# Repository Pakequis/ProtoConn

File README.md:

[![CC BY-SA 4.0][cc-by-sa-shield]][cc-by-sa]
# ProtoConn
A prototype board with connectors for electronic testing and development

This work is licensed under a
[Creative Commons Attribution-ShareAlike 4.0 International License][cc-by-sa].

[![CC BY-SA 4.0][cc-by-sa-image]][cc-by-sa]

[cc-by-sa]: http://creativecommons.org/licenses/by-sa/4.0/
[cc-by-sa-image]: https://licensebuttons.net/l/by-sa/4.0/88x31.png
[cc-by-sa-shield]: https://img.shields.io/badge/License-CC%20BY--SA%204.0-lightgrey.svg

### Overview

This open-hardware prototype board was created as a practical tool to simplify and speed up prototyping. With connectors for various functions, it’s designed to make development more flexible and efficient.

## Demo video:

### Features

Size: 200 x 195 mm dual layer PCB.
- **DE-9 Connector**: Supports serial, joystick, or CAN communication.
- **RCA Connectors**: Includes 3 RCA connectors.
- **Audio Connectors**:
  - 1 P2 audio jack (up to 4 pins).
  - 1 6.3 mm audio jack.
- **Screw Terminals**: Includes 2 screw terminals, one dedicated to power supply.
- **Barrel Connector**: For power input, with integrated 78XX voltage regulator and on/off switch.
- **Potentiometer or Rotary Encoder**: For adjustable input functionality.
- **40-Pin I/O Connector**: Compatible with Raspberry Pi and other Single Board Computers (SBCs).
- **JTAG Connector**: Standard 20-pin JTAG interface.
- **SWD Connectors**:
  - 10-pin SWD with 2.54 mm pitch.
  - 10-pin SWD with 1.27 mm pitch.
- **Programming Connector**: 4-pin interface for STM32 programming.
- **USB/Serial Converter Connector**: Simplifies communication setup.
- **Microcontroller Spaces**: Dedicated spaces for microcontroller boards with widths of 600, 700, 800, and 1000 mils.
- **Arduino Shield Compatibility**: Area for connecting Arduino-compatible shields.
- **Matrix Keypad**: Includes a 12-key matrix keypad.
- **LED Indicators**: 8 LEDs with current-limiting resistors.
- **USB Connectors**:
  - 1 USB Type-A connector.
  - 1 USB Type-B connector.
  - 1 USB Type-C connector.
- **Ground Pad**: Convenient GND pad for prototyping needs.

### Project Files
All project files are organized in the `hardware` folder. If you'd like to manufacture an identical board, the Gerber files necessary for production are available in the `hardware/fab` folder.

Please note that the board does not need to be assembled exactly as shown in the photo. You are free to assemble only the components you want or need, tailoring it to your specific requirements.

Because of this flexibility, the project does not include a complete bill of materials (BOM). Please refer to the notes in the schematic diagram for more detailed information.

Below is an example of an assembled board featuring common black connectors:

## Recommended Components

Here are some specific components that can be used with this board, along with links to purchase them:

- **Colorful Breakable Pin Header 2.54mm Single Row Male**: [Aliexpress](https://s.click.aliexpress.com/e/_op1UJvb)
- **Colorful Breakable Pin Header 2.54mm Single Row Female**: [Aliexpress](https://s.click.aliexpress.com/e/_oB8GhPJ)
- **40-Pin Header for Raspberry Pi**: [Aliexpress](https://s.click.aliexpress.com/e/_oCoQNaN)
- **USB Type-C 02 Connector**: [Aliexpress](https://s.click.aliexpress.com/e/_oo63JmH)
- **Power switch**: [Aliexpress](https://s.click.aliexpress.com/e/_oD5kKvX)

The other components are common and easy to find.

**Affiliate Disclosure**: Some of the links provided in this section are affiliate links. This means that I may earn a commission if you make a purchase through these links, at no additional cost to you. Your support helps to maintain and improve this project.

### Connector Areas

Below are images showcasing the connector areas of the board:

### Top Connector Area

### Bottom Connector Area

### Project Background:
Almost 20 years ago, I purchased a commercial prototype board with multiple connectors that greatly facilitated my work. Unfortunately, I no longer remember where I bought it, and I am unsure if it is still being manufactured. This inspired me to create my own version, customized to meet my specific needs.

The board (circa 2008):

## Contact:

Feel free to reach out to me on social media: @pakequis in any of them...

You can also send me an email at pakequis (Gmail).

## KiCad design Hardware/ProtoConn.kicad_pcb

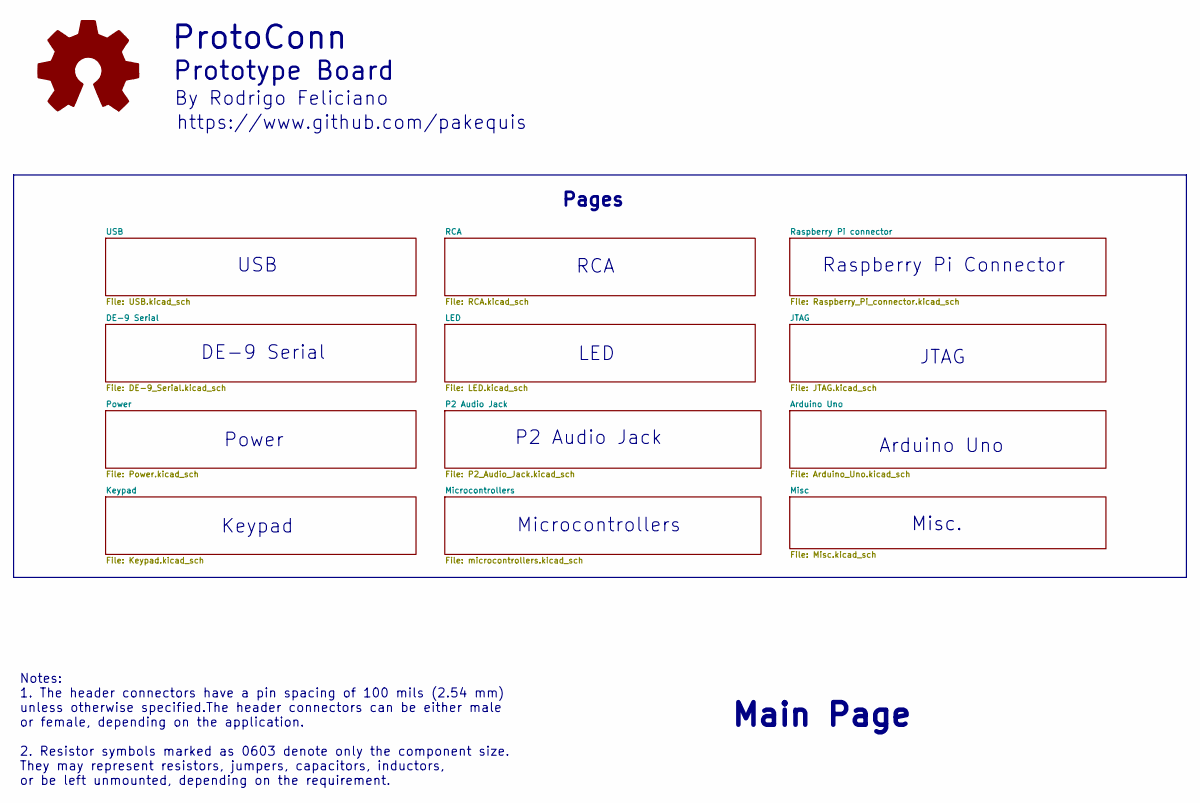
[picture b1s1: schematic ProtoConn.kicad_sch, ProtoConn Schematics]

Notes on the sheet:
USB
Main Page
P2 Audio Jack
Arduino Uno
Microcontrollers
Notes: 1. The header connectors have a pin spacing of 100 mils (2.54 mm) unless otherwise specified.The header connectors can be either male or female, depending on the application. 2. Resistor symbols marked as 0603 denote only the component size. They may represent resistors, jumpers, capacitors,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
Pages
Raspberry Pi Connector
https://www.github.com/pakequis
RCA
Power
JTAG
Keypad
DE-9 Serial
Misc.
LED
Prototype Board
ProtoConn
By Rodrigo Feliciano

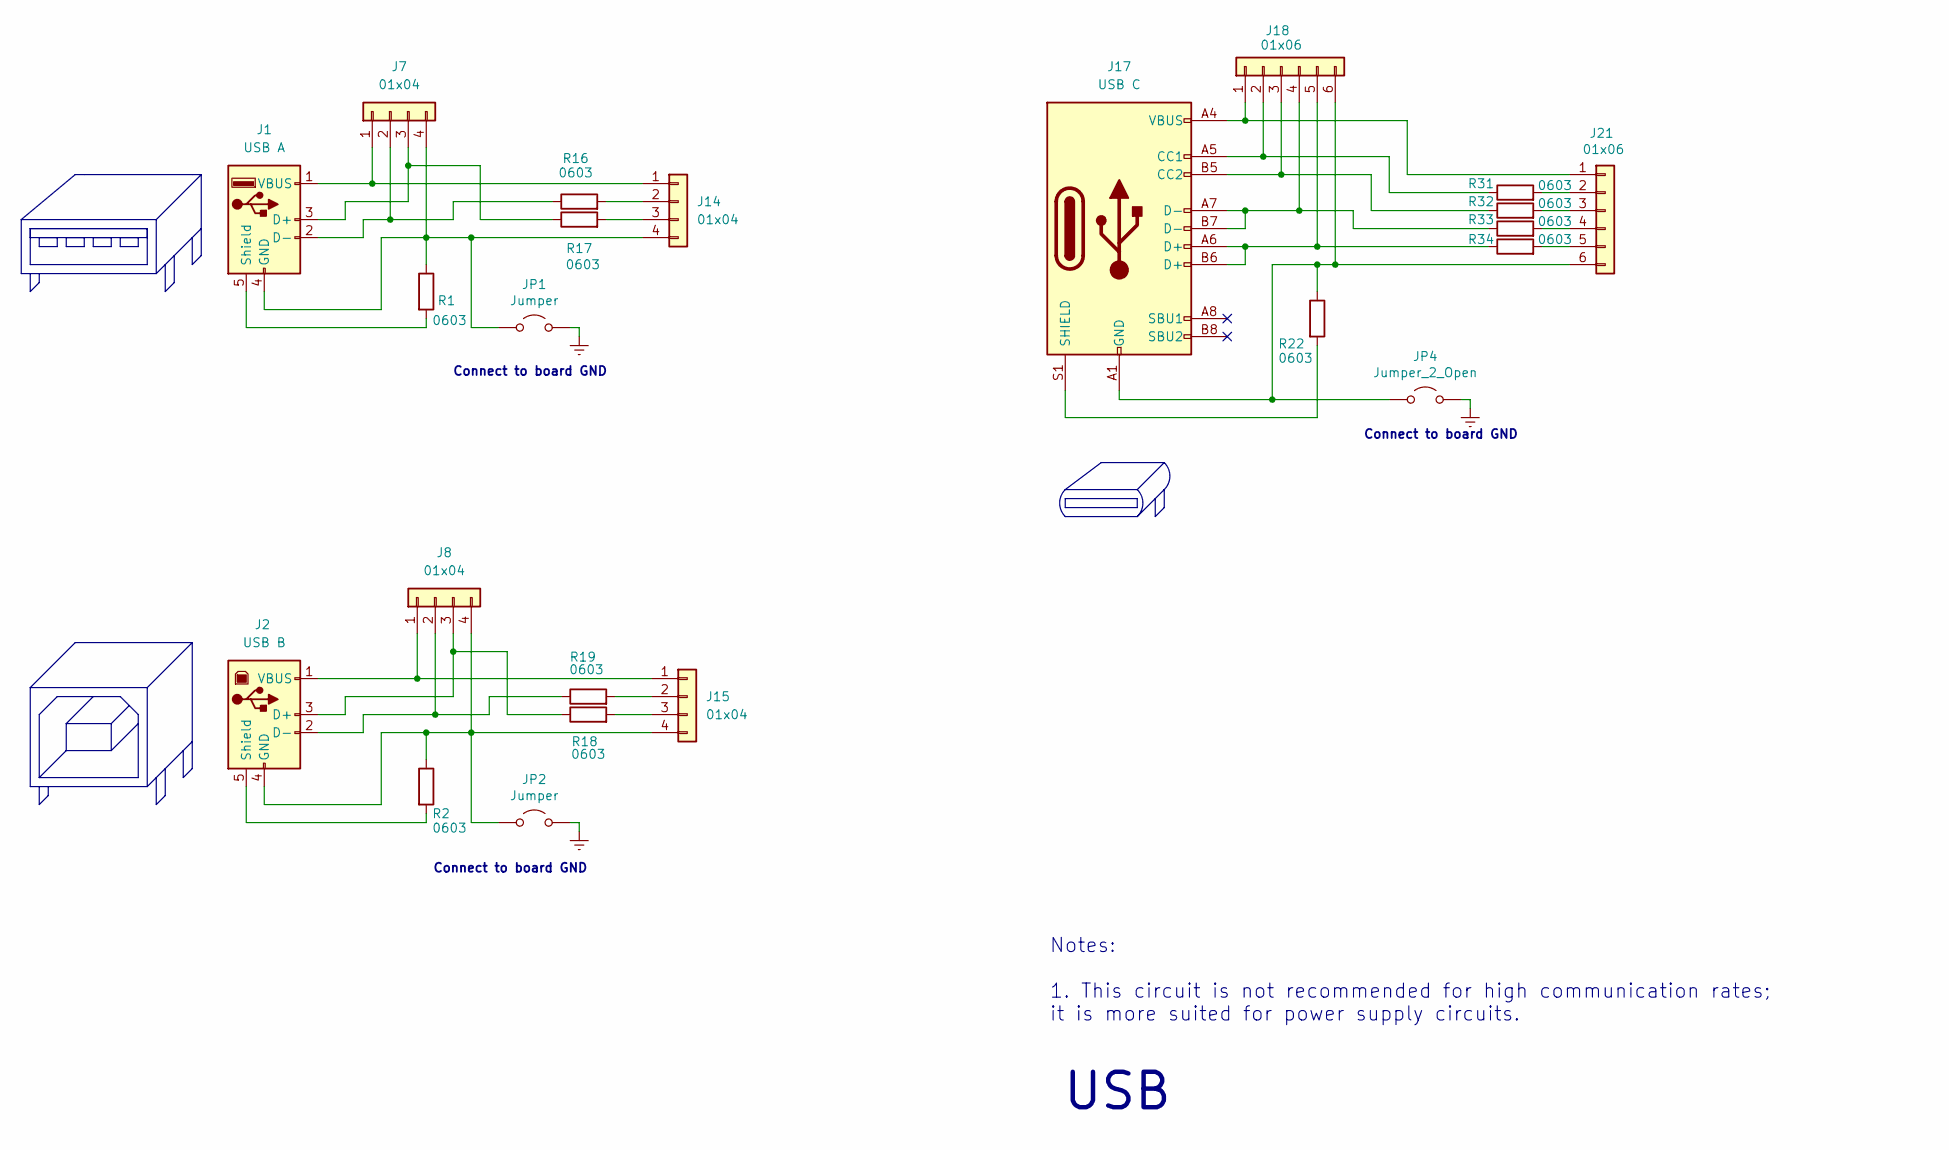
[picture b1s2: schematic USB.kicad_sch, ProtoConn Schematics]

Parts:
J1: USB A; USB_A_CONNFLY_DS1095-WNR0
J2: USB B; USB_B_Lumberg_2411_02_Horizontal
J7, J8, J14, J15: 01x04; PinHeader_1x04_P2.54mm_Vertical
J17: USB C; USB_C_Receptacle_HRO_TYPE-C-31-M-12
J18, J21: 01x06; PinHeader_1x06_P2.54mm_Vertical
JP1, JP2: Jumper; PinHeader_1x02_P2.54mm_Vertical
JP4: Jumper_2_Open; PinHeader_1x02_P2.54mm_Vertical
R1, R2, R16, R17, R18, R19, R22, R31, R32, R33, R34: 0603; R_0603_1608Metric_Pad0.98x0.95mm_HandSolder

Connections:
GNDREF: JP1.1 (A), JP2.1 (A), JP4.1 (A); also elsewhere on the board
unnamed: J1.3 (D+), J7.3, R17.1
unnamed: J1.2 (D-), J7.2, R16.1
unnamed: J1.4 (GND), J7.4, J14.4, JP1.2 (B), R1.1
unnamed: J1.5 (Shield), R1.2
unnamed: J1.1 (VBUS), J7.1, J14.1
unnamed: J2.3 (D+), J8.3, R19.1
unnamed: J2.2 (D-), J8.2, R18.1
unnamed: J2.5 (Shield), R2.2
unnamed: J14.2, R16.2
unnamed: J14.3, R17.2
unnamed: J2.1 (VBUS), J8.1, J15.1
unnamed: J15.2, R18.2
unnamed: J15.3, R19.2
unnamed: J2.4 (GND), J8.4, J15.4, JP2.2 (B), R2.1
unnamed: J17.A5 (CC1), J18.2, R31.1
unnamed: J17.B5 (CC2), J18.3, R32.1
unnamed: J17.S1 (SHIELD), R22.2
unnamed: J17.A4 (VBUS), J17.A9 (VBUS), J17.B4 (VBUS), J17.B9 (VBUS), J18.1, J21.1
unnamed: J17.A7 (D-), J17.B7 (D-), J18.4, R33.1
unnamed: J17.A6 (D+), J17.B6 (D+), J18.5, R34.1
unnamed: J17.A1 (GND), J17.A12 (GND), J17.B1 (GND), J17.B12 (GND), J18.6, J21.6, JP4.2 (B), R22.1
unnamed: J21.2, R31.2
unnamed: J21.3, R32.2
unnamed: J21.4, R33.2
unnamed: J21.5, R34.2

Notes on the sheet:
Connect to board GND
Notes: 1. This circuit is not recommended for high communication rates; it is more suited for power supply circuits.
USB

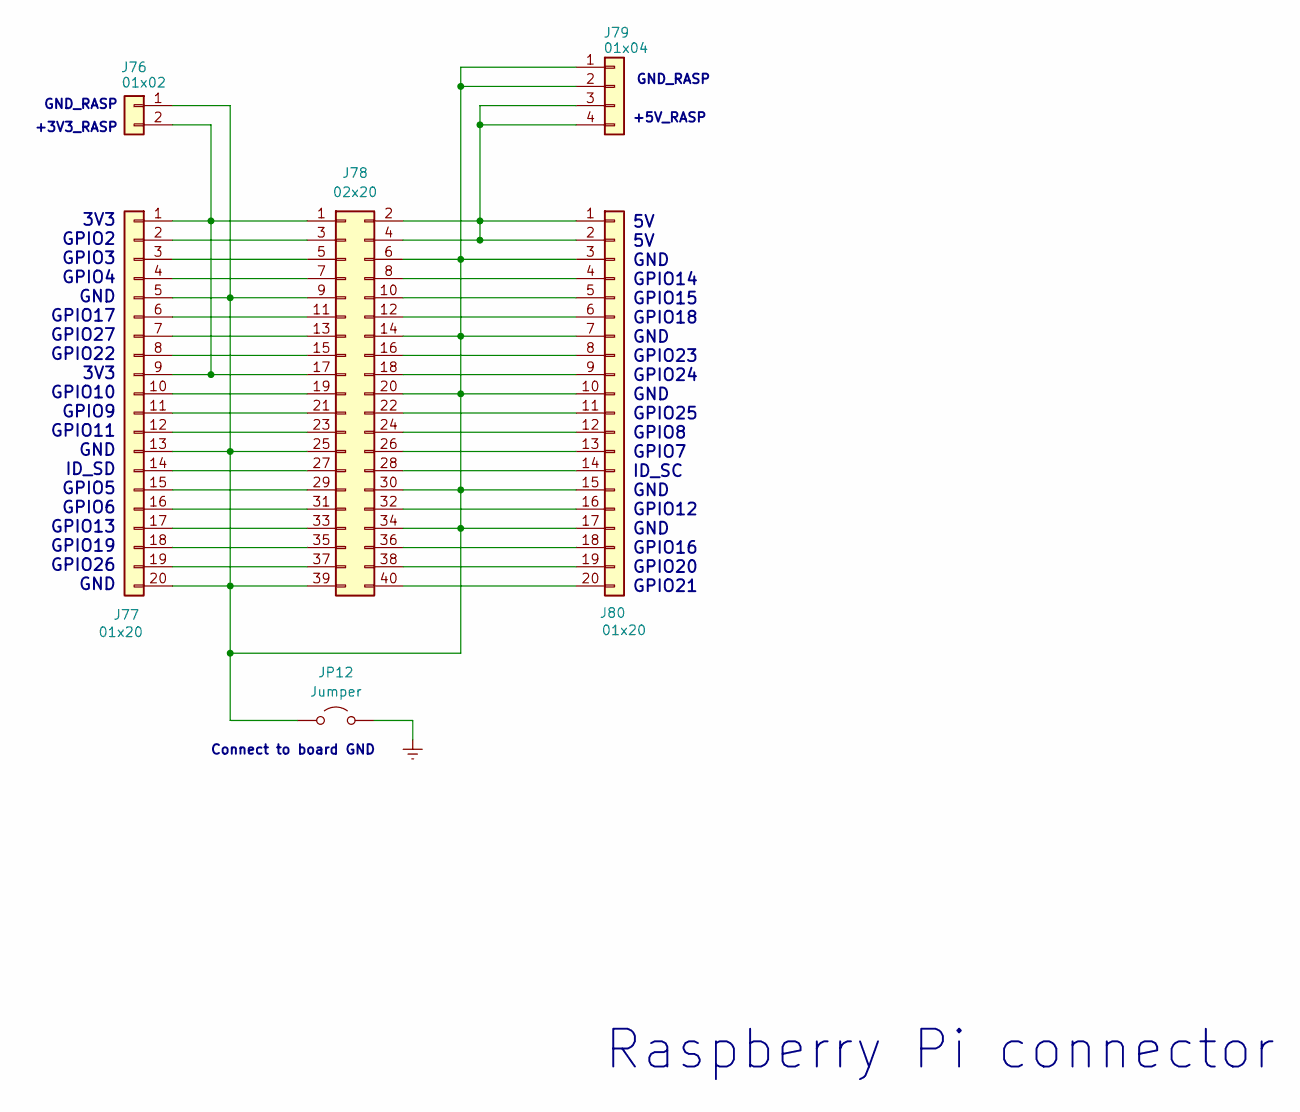
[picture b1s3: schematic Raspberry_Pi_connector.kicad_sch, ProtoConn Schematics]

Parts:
J76: 01x02; PinHeader_1x02_P2.54mm_Vertical
J77, J80: 01x20; PinHeader_1x20_P2.54mm_Vertical
J78: 02x20; PinHeader_2x20_P2.54mm_Vertical
J79: 01x04; PinHeader_1x04_P2.54mm_Vertical
JP12: Jumper; PinHeader_1x02_P2.54mm_Vertical

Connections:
GNDREF: JP12.2 (B); also elsewhere on the board
unnamed: J76.1, J77.5, J77.13, J77.20, J78.6, J78.9, J78.14, J78.20, J78.25, J78.30, J78.34, J78.39, J79.1, J79.2, J80.3, J80.7, J80.10, J80.15, J80.17, JP12.1 (A)
unnamed: J76.2, J77.1, J77.9, J78.1, J78.17
unnamed: J77.2, J78.3
unnamed: J77.3, J78.5
unnamed: J77.4, J78.7
unnamed: J77.6, J78.11
unnamed: J77.7, J78.13
unnamed: J77.8, J78.15
unnamed: J77.10, J78.19
unnamed: J77.11, J78.21
unnamed: J77.12, J78.23
unnamed: J77.14, J78.27
unnamed: J77.15, J78.29
unnamed: J77.16, J78.31
unnamed: J77.17, J78.33
unnamed: J77.18, J78.35
unnamed: J77.19, J78.37
unnamed: J78.2, J78.4, J79.3, J79.4, J80.1, J80.2
unnamed: J78.8, J80.4
unnamed: J78.10, J80.5
unnamed: J78.12, J80.6
unnamed: J78.16, J80.8
unnamed: J78.18, J80.9
unnamed: J78.22, J80.11
unnamed: J78.24, J80.12
unnamed: J78.26, J80.13
unnamed: J78.28, J80.14
unnamed: J78.32, J80.16
unnamed: J78.36, J80.18
unnamed: J78.38, J80.19
unnamed: J78.40, J80.20

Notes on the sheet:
3V3 GPIO2 GPIO3 GPIO4 GND GPIO17 GPIO27 GPIO22 3V3 GPIO10 GPIO9 GPIO11 GND ID_SD GPIO5 GPIO6 GPIO13 GPIO19 GPIO26 GND
GND_RASP
5V 5V GND GPIO14 GPIO15 GPIO18 GND GPIO23 GPIO24 GND GPIO25 GPIO8 GPIO7 ID_SC GND GPIO12 GND GPIO16 GPIO20 GPIO21
Connect to board GND
Raspberry Pi connector
+3V3_RASP
+5V_RASP

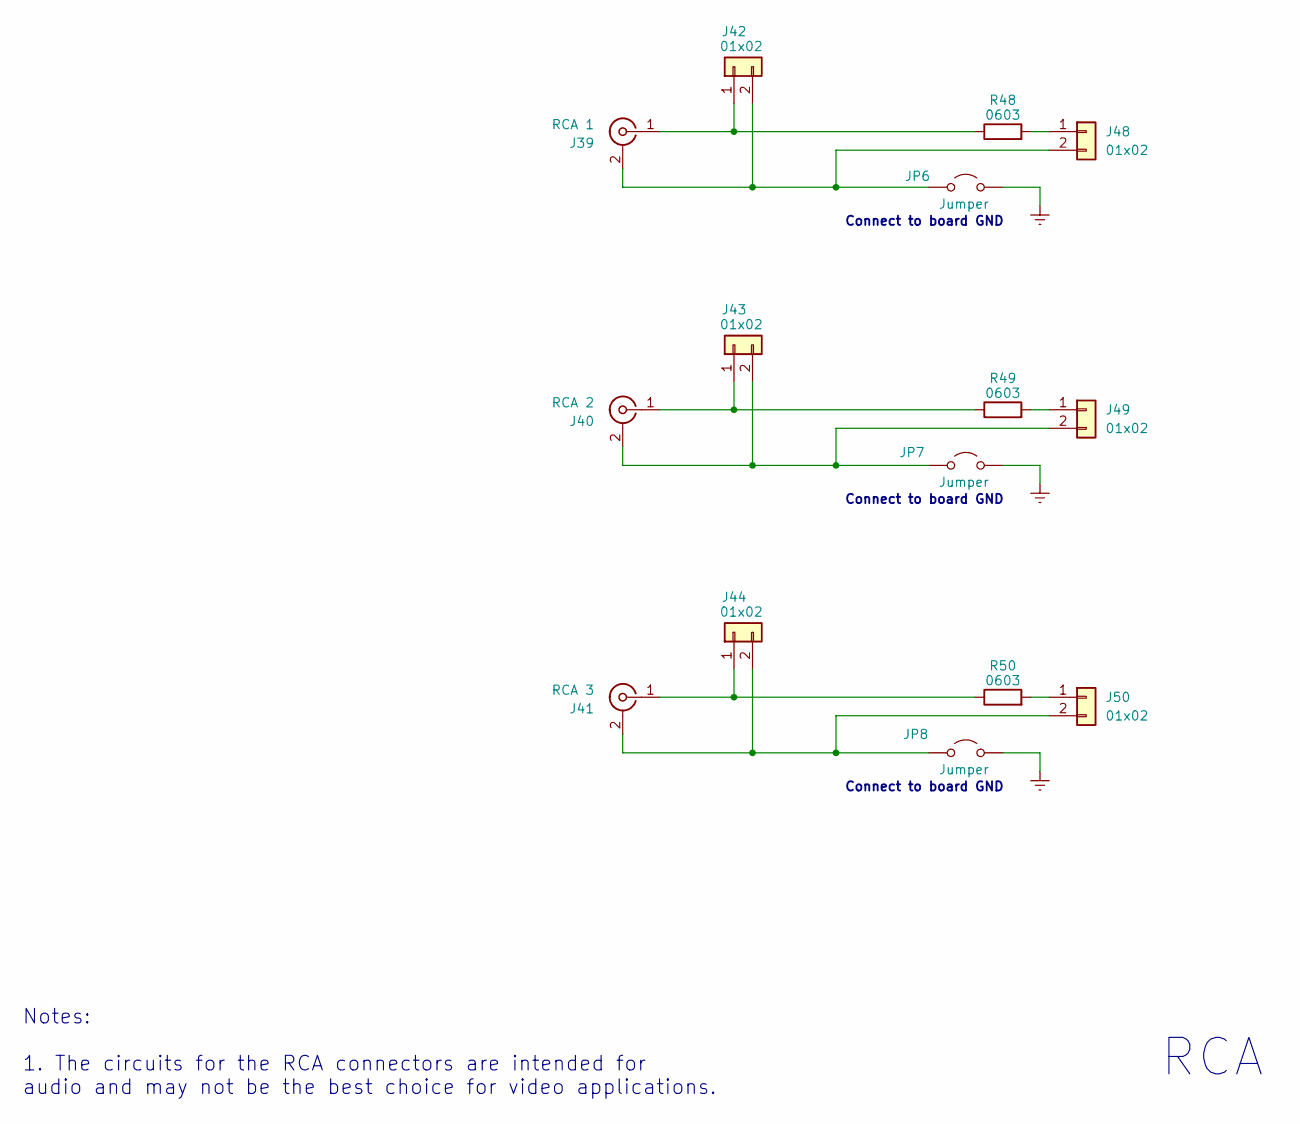
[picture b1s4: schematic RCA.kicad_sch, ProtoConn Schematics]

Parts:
J39: RCA 1; RCA-105-105A
J40: RCA 2; RCA-105-105A
J41: RCA 3; RCA-105-105A
J42, J43, J44, J48, J49, J50: 01x02; PinHeader_1x02_P2.54mm_Vertical
JP6, JP7, JP8: Jumper; PinHeader_1x02_P2.54mm_Vertical
R48, R49, R50: 0603; R_0603_1608Metric_Pad0.98x0.95mm_HandSolder

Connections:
GNDREF: JP6.2 (B), JP7.2 (B), JP8.2 (B); also elsewhere on the board
unnamed: J39.2 (Ext), J42.2, J48.2, JP6.1 (A)
unnamed: J39.1 (In), J42.1, R48.1
unnamed: J40.2 (Ext), J43.2, J49.2, JP7.1 (A)
unnamed: J40.1 (In), J43.1, R49.1
unnamed: J41.2 (Ext), J44.2, J50.2, JP8.1 (A)
unnamed: J41.1 (In), J44.1, R50.1
unnamed: J48.1, R48.2
unnamed: J49.1, R49.2
unnamed: J50.1, R50.2

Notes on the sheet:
Notes: 1. The circuits for the RCA connectors are intended for audio and may not be the best choice for video applications.
RCA
Connect to board GND

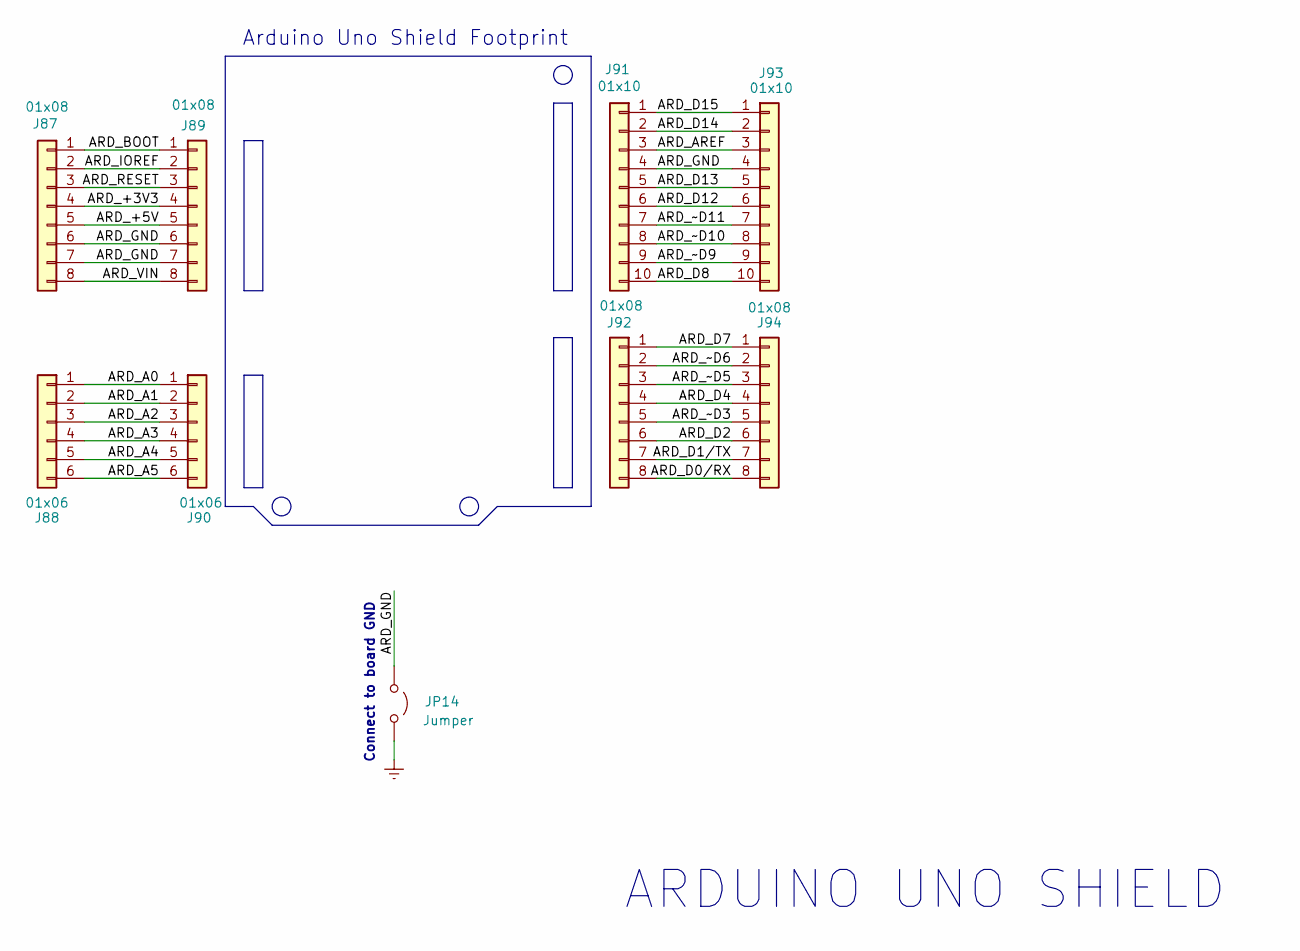
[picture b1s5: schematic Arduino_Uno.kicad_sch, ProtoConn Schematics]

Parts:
J87, J94: 01x08; PinHeader_1x08_P2.54mm_Vertical
J88: 01x06; PinHeader_1x06_P2.54mm_Vertical
J89, J92: 01x08; PinSocket_1x08_P2.54mm_Vertical
J90: 01x06; PinSocket_1x06_P2.54mm_Vertical
J91: 01x10; PinSocket_1x10_P2.54mm_Vertical
J93: 01x10; PinHeader_1x10_P2.54mm_Vertical
JP14: Jumper; PinHeader_1x02_P2.54mm_Vertical

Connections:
/Arduino Uno/ARD_+3V3: J87.4, J89.4
/Arduino Uno/ARD_+5V: J87.5, J89.5
/Arduino Uno/ARD_A0: J88.1, J90.1
/Arduino Uno/ARD_A1: J88.2, J90.2
/Arduino Uno/ARD_A2: J88.3, J90.3
/Arduino Uno/ARD_A3: J88.4, J90.4
/Arduino Uno/ARD_A4: J88.5, J90.5
/Arduino Uno/ARD_A5: J88.6, J90.6
/Arduino Uno/ARD_AREF: J91.3, J93.3
/Arduino Uno/ARD_BOOT: J87.1, J89.1
/Arduino Uno/ARD_D0/RX: J92.8, J94.8
/Arduino Uno/ARD_D1/TX: J92.7, J94.7
/Arduino Uno/ARD_D2: J92.6, J94.6
/Arduino Uno/ARD_D4: J92.4, J94.4
/Arduino Uno/ARD_D7: J92.1, J94.1
/Arduino Uno/ARD_D8: J91.10, J93.10
/Arduino Uno/ARD_D12: J91.6, J93.6
/Arduino Uno/ARD_D13: J91.5, J93.5
/Arduino Uno/ARD_D14: J91.2, J93.2
/Arduino Uno/ARD_D15: J91.1, J93.1
/Arduino Uno/ARD_GND: J87.6, J87.7, J89.6, J89.7, J91.4, J93.4, JP14.1 (A)
/Arduino Uno/ARD_IOREF: J87.2, J89.2
/Arduino Uno/ARD_RESET: J87.3, J89.3
/Arduino Uno/ARD_VIN: J87.8, J89.8
/Arduino Uno/ARD_~D3: J92.5, J94.5
/Arduino Uno/ARD_~D5: J92.3, J94.3
/Arduino Uno/ARD_~D6: J92.2, J94.2
/Arduino Uno/ARD_~D9: J91.9, J93.9
/Arduino Uno/ARD_~D10: J91.8, J93.8
/Arduino Uno/ARD_~D11: J91.7, J93.7
GNDREF: JP14.2 (B); also elsewhere on the board

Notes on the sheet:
Arduino Uno Shield Footprint
ARDUINO UNO SHIELD
Connect to board GND

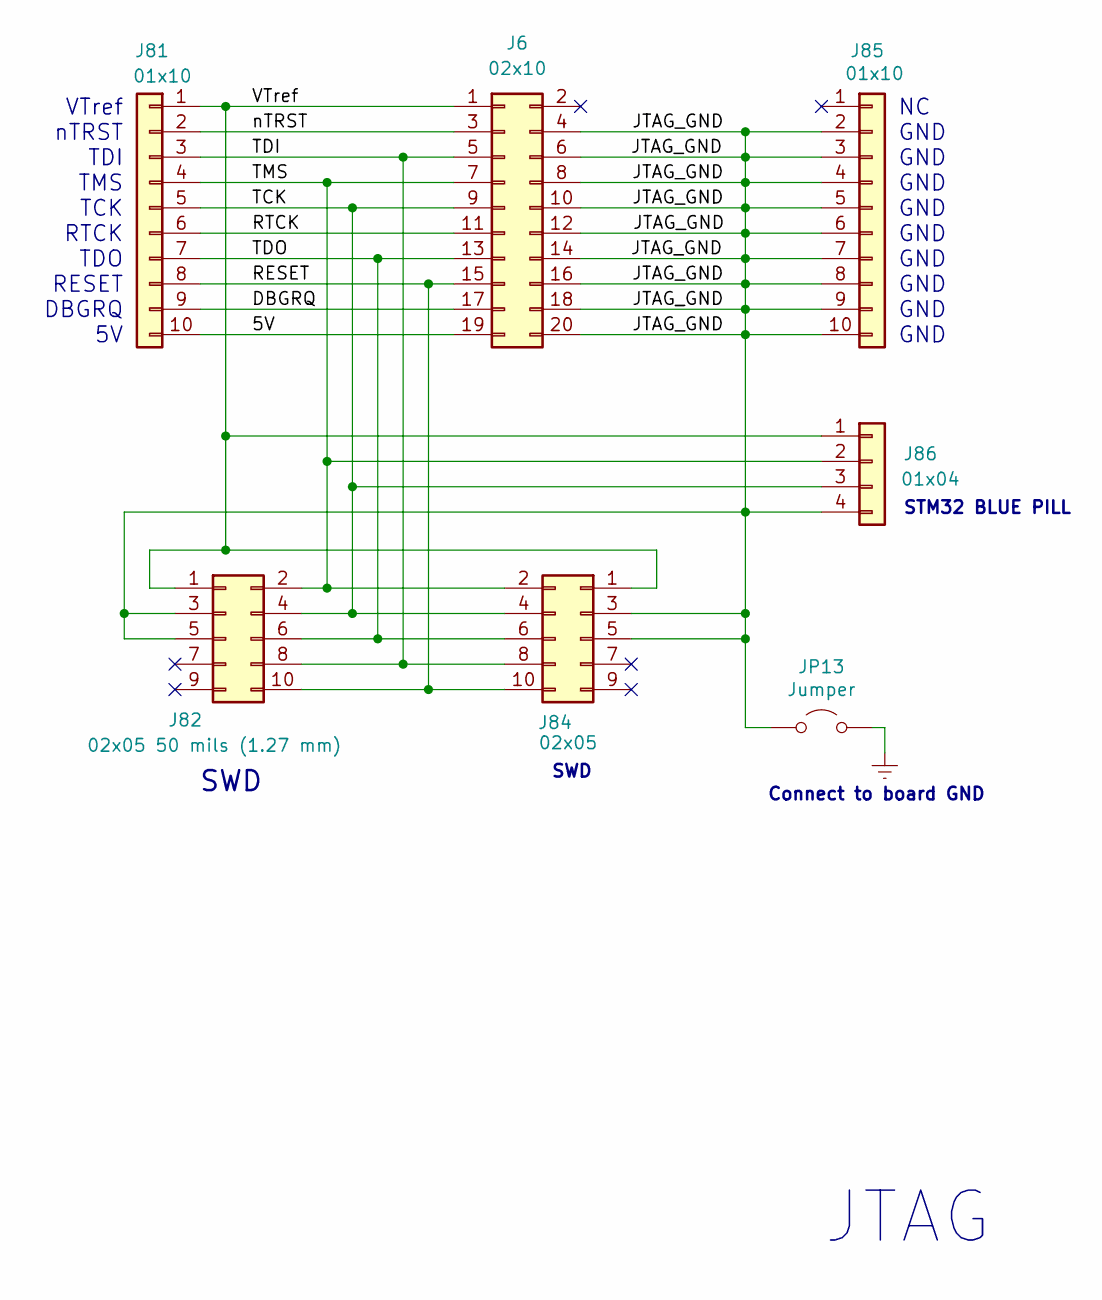
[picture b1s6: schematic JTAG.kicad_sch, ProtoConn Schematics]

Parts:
J6: 02x10; PinHeader_2x10_P2.54mm_Vertical
J81, J85: 01x10; PinHeader_1x10_P2.54mm_Vertical
J82: 02x05 50 mils (1.27 mm); PinHeader_2x05_P1.27mm_Vertical
J84: 02x05; PinHeader_2x05_P2.54mm_Vertical
J86: 01x04; PinHeader_1x04_P2.54mm_Vertical
JP13: Jumper; PinHeader_1x02_P2.54mm_Vertical

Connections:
/JTAG/5V: J6.19, J81.10
/JTAG/DBGRQ: J6.17, J81.9
/JTAG/JTAG_GND: J6.4, J6.6, J6.8, J6.10, J6.12, J6.14, J6.16, J6.18, J6.20, J82.3, J82.5, J84.3, J84.5, J85.2, J85.3, J85.4, J85.5, J85.6, J85.7, J85.8, J85.9, J85.10, J86.4, JP13.1 (A)
/JTAG/RESET: J6.15, J81.8, J82.10, J84.10
/JTAG/RTCK: J6.11, J81.6
/JTAG/TCK: J6.9, J81.5, J82.4, J84.4, J86.3
/JTAG/TDI: J6.5, J81.3, J82.8, J84.8
/JTAG/TDO: J6.13, J81.7, J82.6, J84.6
/JTAG/TMS: J6.7, J81.4, J82.2, J84.2, J86.2
/JTAG/VTref: J6.1, J81.1, J82.1, J84.1, J86.1
/JTAG/nTRST: J6.3, J81.2
GNDREF: JP13.2 (B); also elsewhere on the board

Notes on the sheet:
STM32 BLUE PILL
SWD
JTAG
VTref nTRST TDI TMS TCK RTCK TDO RESET DBGRQ 5V
Connect to board GND
NC GND GND GND GND GND GND GND GND GND

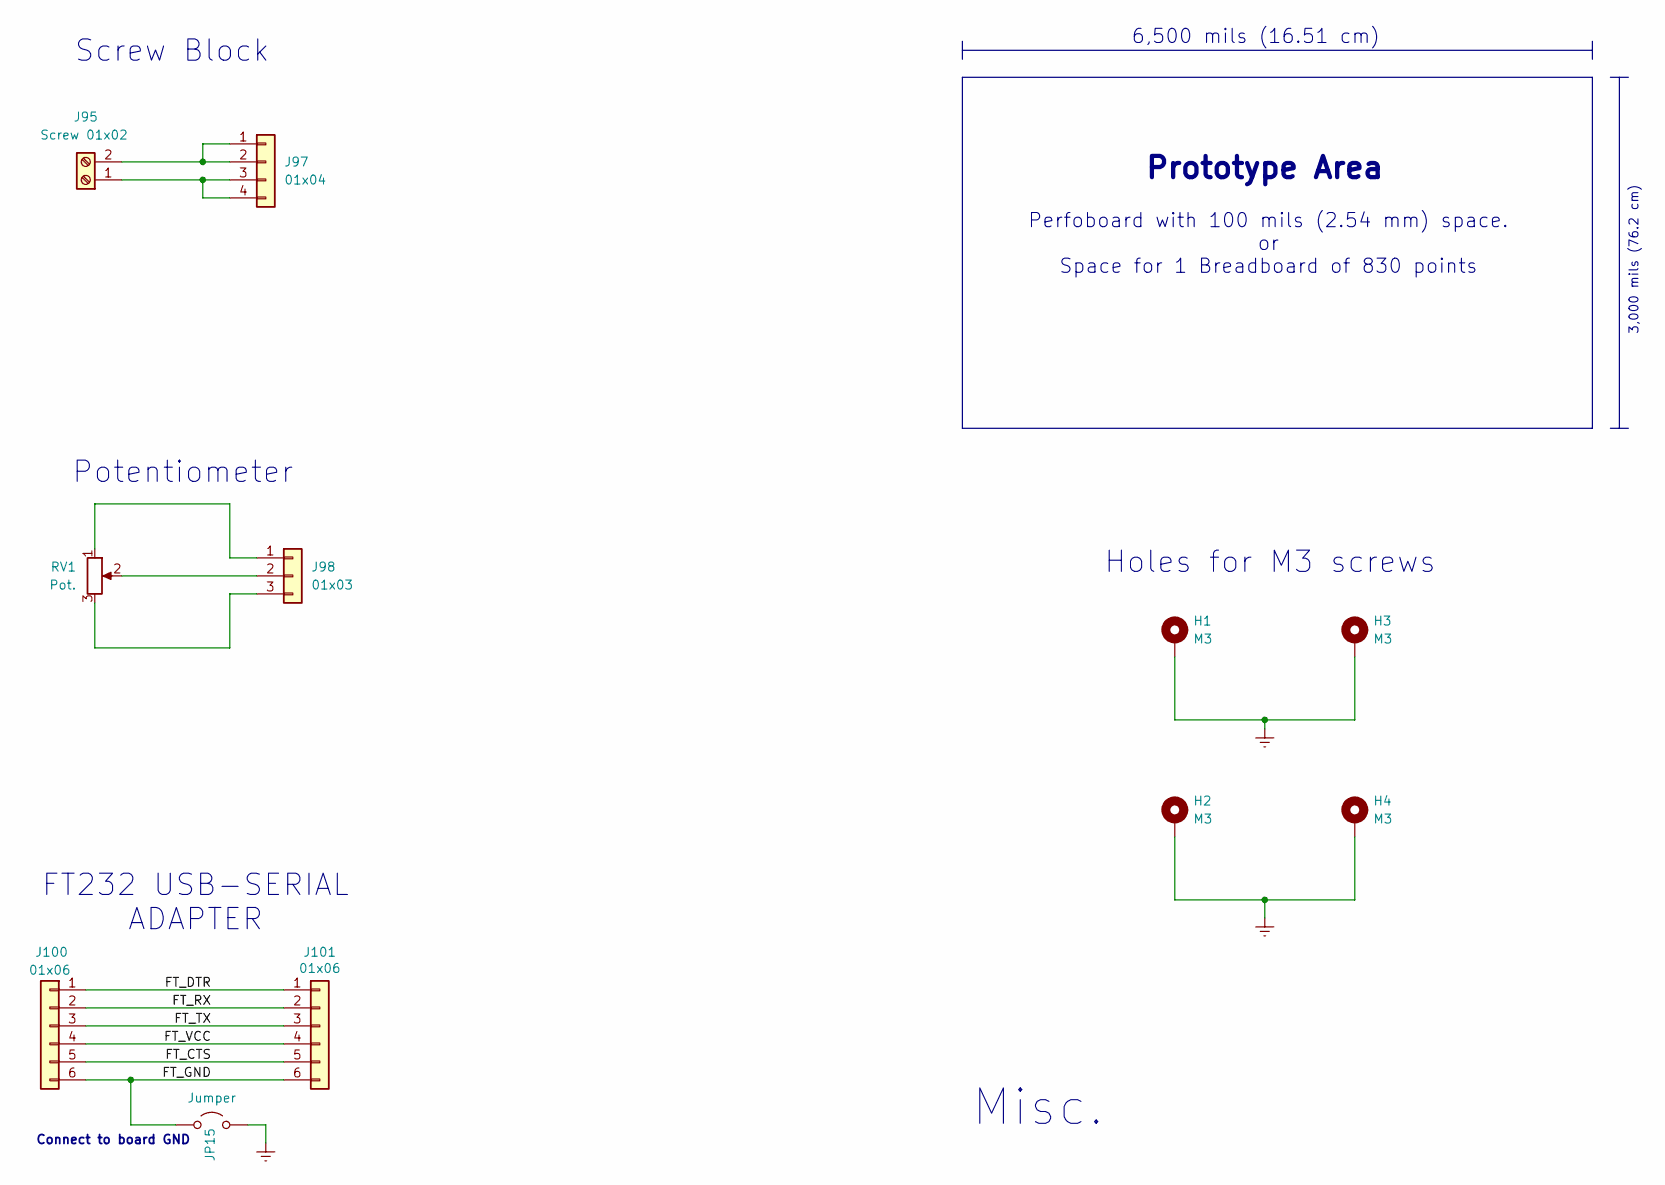
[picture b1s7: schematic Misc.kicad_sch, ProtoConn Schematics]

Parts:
H1, H2, H3, H4: M3; MountingHole_3.2mm_M3_DIN965_Pad_TopBottom
J95: Screw 01x02; TerminalBlock_bornier-2_P5.08mm
J97: 01x04; PinHeader_1x04_P2.54mm_Vertical
J98: 01x03; PinSocket_1x03_P2.54mm_Vertical
J100, J101: 01x06; PinHeader_1x06_P2.54mm_Vertical
JP15: Jumper; PinHeader_1x02_P2.54mm_Vertical
RV1: Pot.; Potentiometer_Alpha_RD901F-40-00D_Single_Vertical

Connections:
/Misc/FT_CTS: J100.5, J101.5
/Misc/FT_DTR: J100.1, J101.1
/Misc/FT_GND: J100.6, J101.6, JP15.1 (A)
/Misc/FT_RX: J100.2, J101.2
/Misc/FT_TX: J100.3, J101.3
/Misc/FT_VCC: J100.4, J101.4
GNDREF: H1.1, H2.1, H3.1, H4.1, JP15.2 (B); also elsewhere on the board
unnamed: J95.1, J97.3, J97.4
unnamed: J95.2, J97.1, J97.2
unnamed: J98.1, RV1.1
unnamed: J98.2, RV1.2
unnamed: J98.3, RV1.3

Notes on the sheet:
Connect to board GND
6,500 mils (16.51 cm)
Misc.
Screw Block
Perfoboard with 100 mils (2.54 mm) space. or Space for 1 Breadboard of 830 points
Holes for M3 screws
Potentiometer
Prototype Area
3,000 mils (76.2 cm)
FT232 USB-SERIAL ADAPTER

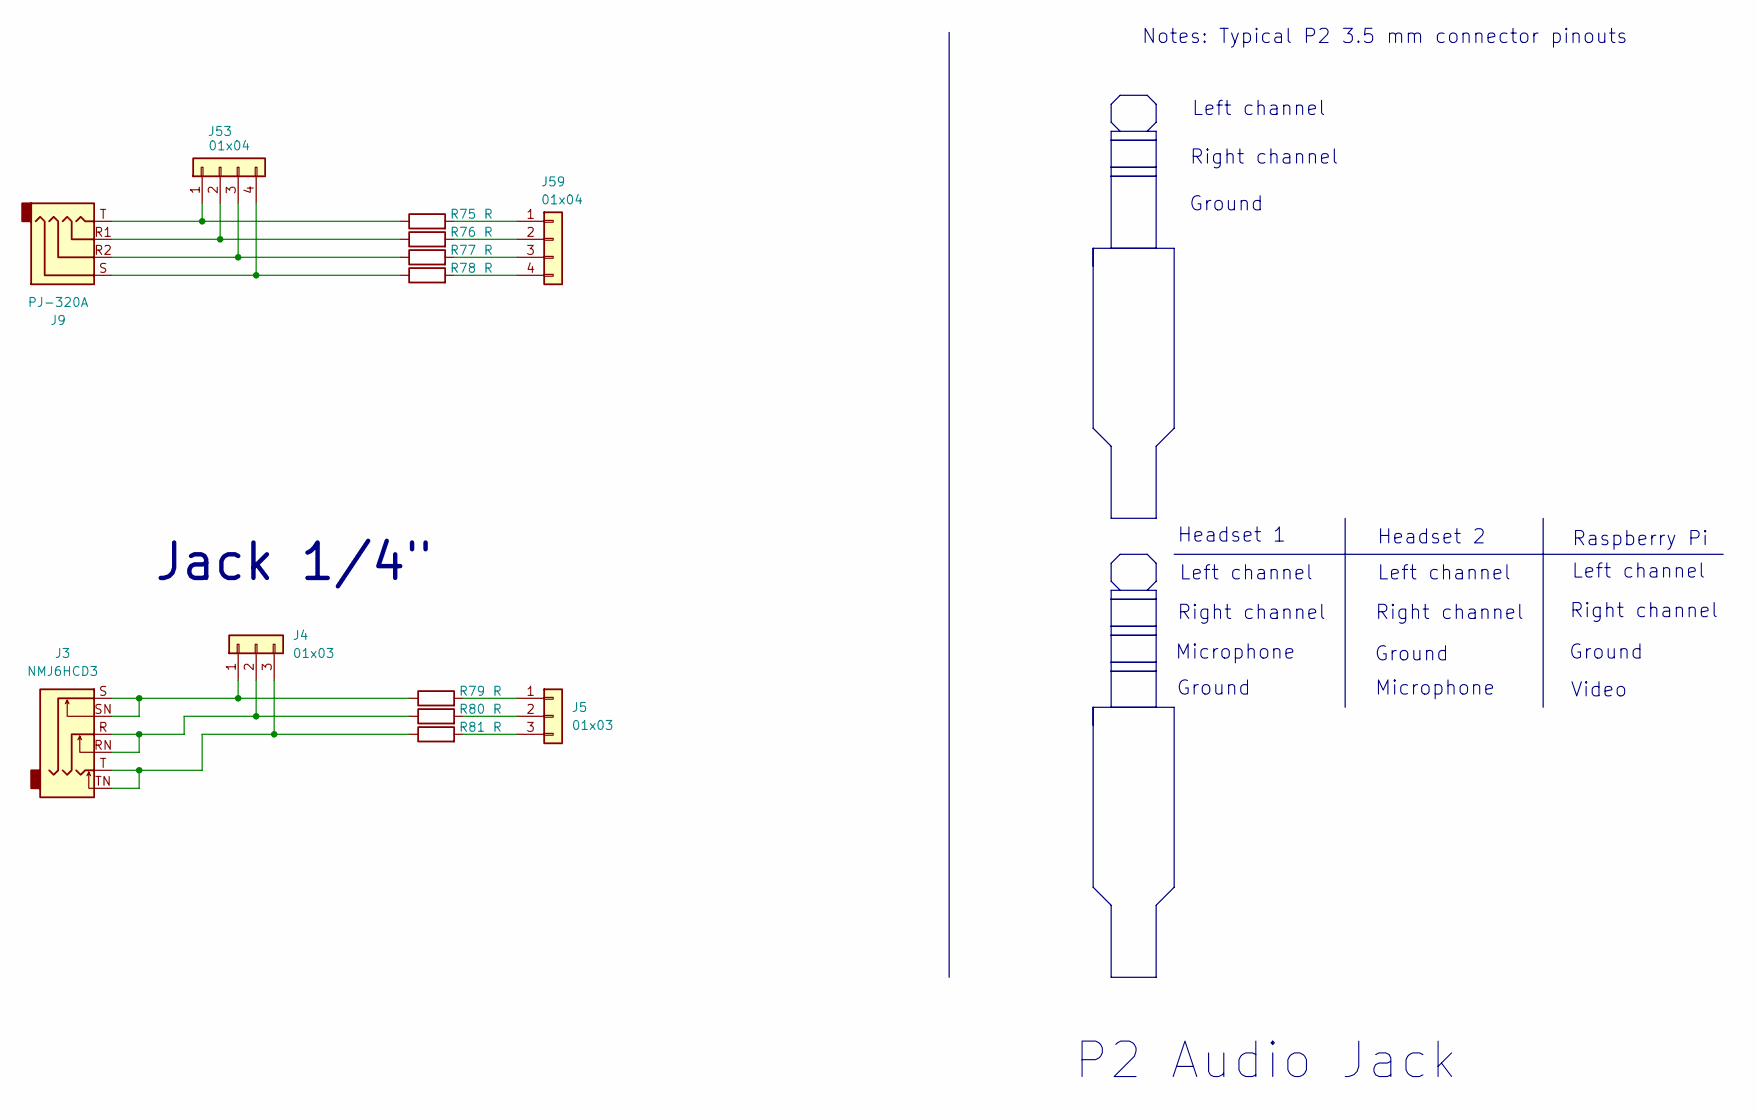
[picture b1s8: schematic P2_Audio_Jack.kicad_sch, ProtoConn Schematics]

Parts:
J3: NMJ6HCD3; Jack_6.35mm_Neutrik_NMJ6HCD3_Horizontal
J4, J5: 01x03; PinSocket_1x03_P2.54mm_Vertical
J9: PJ-320A
J53, J59: 01x04; PinHeader_1x04_P2.54mm_Vertical
R75, R76, R77, R78, R79, R80, R81: R; R_0603_1608Metric_Pad0.98x0.95mm_HandSolder

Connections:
unnamed: J3.S, J3.SN, J4.1, R79.1
unnamed: J3.R, J3.RN, J4.2, R80.1
unnamed: J3.T, J3.TN, J4.3, R81.1
unnamed: J5.1, R79.2
unnamed: J5.2, R80.2
unnamed: J5.3, R81.2
unnamed: J9.T, J53.1, R75.1
unnamed: J9.R1, J53.2, R76.1
unnamed: J9.R2, J53.3, R77.1
unnamed: J9.S, J53.4, R78.1
unnamed: J59.1, R75.2
unnamed: J59.2, R76.2
unnamed: J59.3, R77.2
unnamed: J59.4, R78.2

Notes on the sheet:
Ground
Notes: Typical P2 3.5 mm connector pinouts
Left channel
Microphone
Right channel
Jack 1/4"
P2 Audio Jack
Raspberry Pi
Video
Headset 1
Headset 2

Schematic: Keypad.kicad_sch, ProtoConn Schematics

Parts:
J36: 01x02; PinHeader_1x02_P2.54mm_Vertical
J37: 01x04; PinHeader_1x04_P2.54mm_Vertical
J38: 01x03; PinSocket_1x03_P2.54mm_Vertical
R39, R40, R41: 0603; R_0603_1608Metric_Pad0.98x0.95mm_HandSolder
SW3, SW4, SW5, SW6, SW7, SW8, SW9, SW10, SW11, SW12, SW13, SW14: SW_Push_45deg; SW_PUSH_6mm

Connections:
unnamed: J36.1, J36.2, R39.1, R40.1, R41.1
unnamed: J37.1, SW3.1, SW7.1, SW11.1
unnamed: J37.2, SW4.1, SW8.1, SW12.1
unnamed: J37.3, SW5.1, SW9.1, SW13.1
unnamed: J37.4, SW6.1, SW10.1, SW14.1
unnamed: J38.1, R39.2, SW11.2, SW12.2, SW13.2, SW14.2
unnamed: J38.2, R40.2, SW7.2, SW8.2, SW9.2, SW10.2
unnamed: J38.3, R41.2, SW3.2, SW4.2, SW5.2, SW6.2

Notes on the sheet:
COL1 COL2 COL3
R1 R2 R3 R4
Notes: 1. The resistors are for pull-up or pull-down purposes as needed.
Keypad

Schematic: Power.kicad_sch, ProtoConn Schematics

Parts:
C1, C5: C; CP_Radial_D5.0mm_P2.50mm
C3, C7: C 0603; C_0603_1608Metric_Pad1.08x0.95mm_HandSolder
D1: LED; LED_0603_1608Metric
J26: Barrel Jack; BarrelJack_Kycon_KLDX-0202-xC_Horizontal
J28: Screw 01x02; TerminalBlock_bornier-2_P5.08mm
J30: 01x02; PinHeader_1x02_P2.54mm_Vertical
J32: 02x04; PinHeader_2x04_P2.54mm_Vertical
J34: 01x06; PinHeader_1x06_P2.54mm_Vertical
R37: 0603; R_0603_1608Metric_Pad0.98x0.95mm_HandSolder
SW1: SW_SPDT; SW_Slide_SPDT_Straight_CK_OS102011MS2Q
U1: LM78XX TO220; TO-220-3_Vertical

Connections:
GNDREF: C1.2, C3.2, C5.2, C7.2, J26.2, J26.3, J28.1, J30.2, J32.1, J32.3, J32.5, J32.7, J34.4, J34.5, J34.6, R37.2, U1.2 (GND); also elsewhere on the board
unnamed: C1.1, C3.1, D1.2 (A), SW1.1 (A), U1.1 (VI)
unnamed: D1.1 (K), R37.1
unnamed: J26.1, J28.2, J30.1, SW1.2 (B)
unnamed: J32.2, J32.4, J32.6, J32.8, SW1.3 (C)
unnamed: C5.1, C7.1, J34.1, J34.2, J34.3, U1.3 (VO)

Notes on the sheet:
Notes: 1. Barrel Jack connected for center positive power supply.
POWER
+ V GND

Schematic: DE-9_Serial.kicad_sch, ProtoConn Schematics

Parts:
J22: 01x04; PinHeader_1x04_P2.54mm_Vertical
J23: DE9; DSUB-9_Female_Horizontal_P2.77x2.84mm_EdgePinOffset4.94mm_H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
J24: 01x09; PinHeader_1x09_P2.54mm_Vertical
J25: 01x06; PinHeader_1x06_P2.54mm_Vertical
JP5: Jumper; PinHeader_1x02_P2.54mm_Vertical
R35, R36: 0603; R_0603_1608Metric_Pad0.98x0.95mm_HandSolder

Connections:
GNDREF: JP5.1 (A); also elsewhere on the board
unnamed: J22.1, J23.1, J24.1, R35.2
unnamed: J22.2, J23.6, J24.6
unnamed: J22.3, J23.8, J24.8, R35.1
unnamed: J22.4, J23.5, J24.5, J25.5
unnamed: J23.0 (PAD), JP5.2 (B)
unnamed: J23.2, J24.2, J25.1, R36.2
unnamed: J23.3, J24.3, J25.2
unnamed: J23.4, J24.4, J25.4
unnamed: J23.7, J24.7, J25.3, R36.1
unnamed: J23.9, J24.9, J25.6

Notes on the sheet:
CAN Low GND CAN High SHIELD
Notes: 1. The resistors are for CAN termination or can be left unmounted, depending on the application. 2. The DE9 connector will be male or female based on the application requirements. 3. The markings are for the most common types of communication interfaces and may vary for other applications.
GND CTS+ RTS+ RXD+ RXD- CTS- RTS- TXD+ TXD-
RS422 - RS485
RS232
DCD RXD TXD DTR GND DSR RTS CTS RI
Connect to board GND
CAN Low GND CAN High SP SHIELD VB+
CAN 1
DE-9 Serial
CAN 2

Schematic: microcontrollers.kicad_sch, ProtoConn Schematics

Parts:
J61, J63, J69, J73: 01x12; PinHeader_1x12_P2.54mm_Vertical
J62, J68, J70, J71: 01x10; PinHeader_1x10_P2.54mm_Vertical
J64, J66: 01x12; PinSocket_1x12_P2.54mm_Vertical
J65, J67: 01x10; PinSocket_1x10_P2.54mm_Vertical
J72, J74, J75: 01x20; PinSocket_1x20_P2.54mm_Vertical

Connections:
/Microcontrollers/uc_pin1: J61.1, J63.1, J64.1
/Microcontrollers/uc_pin2: J61.2, J63.2, J64.2
/Microcontrollers/uc_pin3: J61.3, J63.3, J64.3
/Microcontrollers/uc_pin4: J61.4, J63.4, J64.4
/Microcontrollers/uc_pin5: J61.5, J63.5, J64.5
/Microcontrollers/uc_pin6: J61.6, J63.6, J64.6
/Microcontrollers/uc_pin7: J61.7, J63.7, J64.7
/Microcontrollers/uc_pin8: J61.8, J63.8, J64.8
/Microcontrollers/uc_pin9: J61.9, J63.9, J64.9
/Microcontrollers/uc_pin10: J61.10, J63.10, J64.10
/Microcontrollers/uc_pin11: J61.11, J63.11, J64.11
/Microcontrollers/uc_pin12: J61.12, J63.12, J64.12
/Microcontrollers/uc_pin13: J62.1, J65.1, J68.1
/Microcontrollers/uc_pin14: J62.2, J65.2, J68.2
/Microcontrollers/uc_pin15: J62.3, J65.3, J68.3
/Microcontrollers/uc_pin16: J62.4, J65.4, J68.4
/Microcontrollers/uc_pin17: J62.5, J65.5, J68.5
/Microcontrollers/uc_pin18: J62.6, J65.6, J68.6
/Microcontrollers/uc_pin19: J62.7, J65.7, J68.7
/Microcontrollers/uc_pin20: J62.8, J65.8, J68.8
/Microcontrollers/uc_pin21: J62.9, J65.9, J68.9
/Microcontrollers/uc_pin22: J62.10, J65.10, J68.10
/Microcontrollers/uc_pin23: J67.10, J70.10, J71.10, J72.20, J74.20, J75.20
/Microcontrollers/uc_pin24: J67.9, J70.9, J71.9, J72.19, J74.19, J75.19
/Microcontrollers/uc_pin25: J67.8, J70.8, J71.8, J72.18, J74.18, J75.18
/Microcontrollers/uc_pin26: J67.7, J70.7, J71.7, J72.17, J74.17, J75.17
/Microcontrollers/uc_pin27: J67.6, J70.6, J71.6, J72.16, J74.16, J75.16
/Microcontrollers/uc_pin28: J67.5, J70.5, J71.5, J72.15, J74.15, J75.15
/Microcontrollers/uc_pin29: J67.4, J70.4, J71.4, J72.14, J74.14, J75.14
/Microcontrollers/uc_pin30: J67.3, J70.3, J71.3, J72.13, J74.13, J75.13
/Microcontrollers/uc_pin31: J67.2, J70.2, J71.2, J72.12, J74.12, J75.12
/Microcontrollers/uc_pin32: J67.1, J70.1, J71.1, J72.11, J74.11, J75.11
/Microcontrollers/uc_pin33: J66.12, J69.12, J72.10, J73.12, J74.10, J75.10
/Microcontrollers/uc_pin34: J66.11, J69.11, J72.9, J73.11, J74.9, J75.9
/Microcontrollers/uc_pin35: J66.10, J69.10, J72.8, J73.10, J74.8, J75.8
/Microcontrollers/uc_pin36: J66.9, J69.9, J72.7, J73.9, J74.7, J75.7
/Microcontrollers/uc_pin37: J66.8, J69.8, J72.6, J73.8, J74.6, J75.6
/Microcontrollers/uc_pin38: J66.7, J69.7, J72.5, J73.7, J74.5, J75.5
/Microcontrollers/uc_pin39: J66.6, J69.6, J72.4, J73.6, J74.4, J75.4
/Microcontrollers/uc_pin40: J66.5, J69.5, J72.3, J73.5, J74.3, J75.3
/Microcontrollers/uc_pin41: J66.4, J69.4, J72.2, J73.4, J74.2, J75.2
/Microcontrollers/uc_pin42: J66.3, J69.3, J72.1, J73.3, J74.1, J75.1
/Microcontrollers/uc_pin43: J66.2, J69.2, J73.2
/Microcontrollers/uc_pin44: J66.1, J69.1, J73.1

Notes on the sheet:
ESP32
Raspberry Pi Pico
STM32 Pill and Arduino mini Pro
Microcontrollers connectors
Adafruit Feather
Up to 40 Pins 600 mils (15.24 mm) Up to 40 pins 700 mils (17.78 mm)
Up to 44 pins 1" (25.4 mm)
Up to 40 Pins 800 mils (20,32 mm)
